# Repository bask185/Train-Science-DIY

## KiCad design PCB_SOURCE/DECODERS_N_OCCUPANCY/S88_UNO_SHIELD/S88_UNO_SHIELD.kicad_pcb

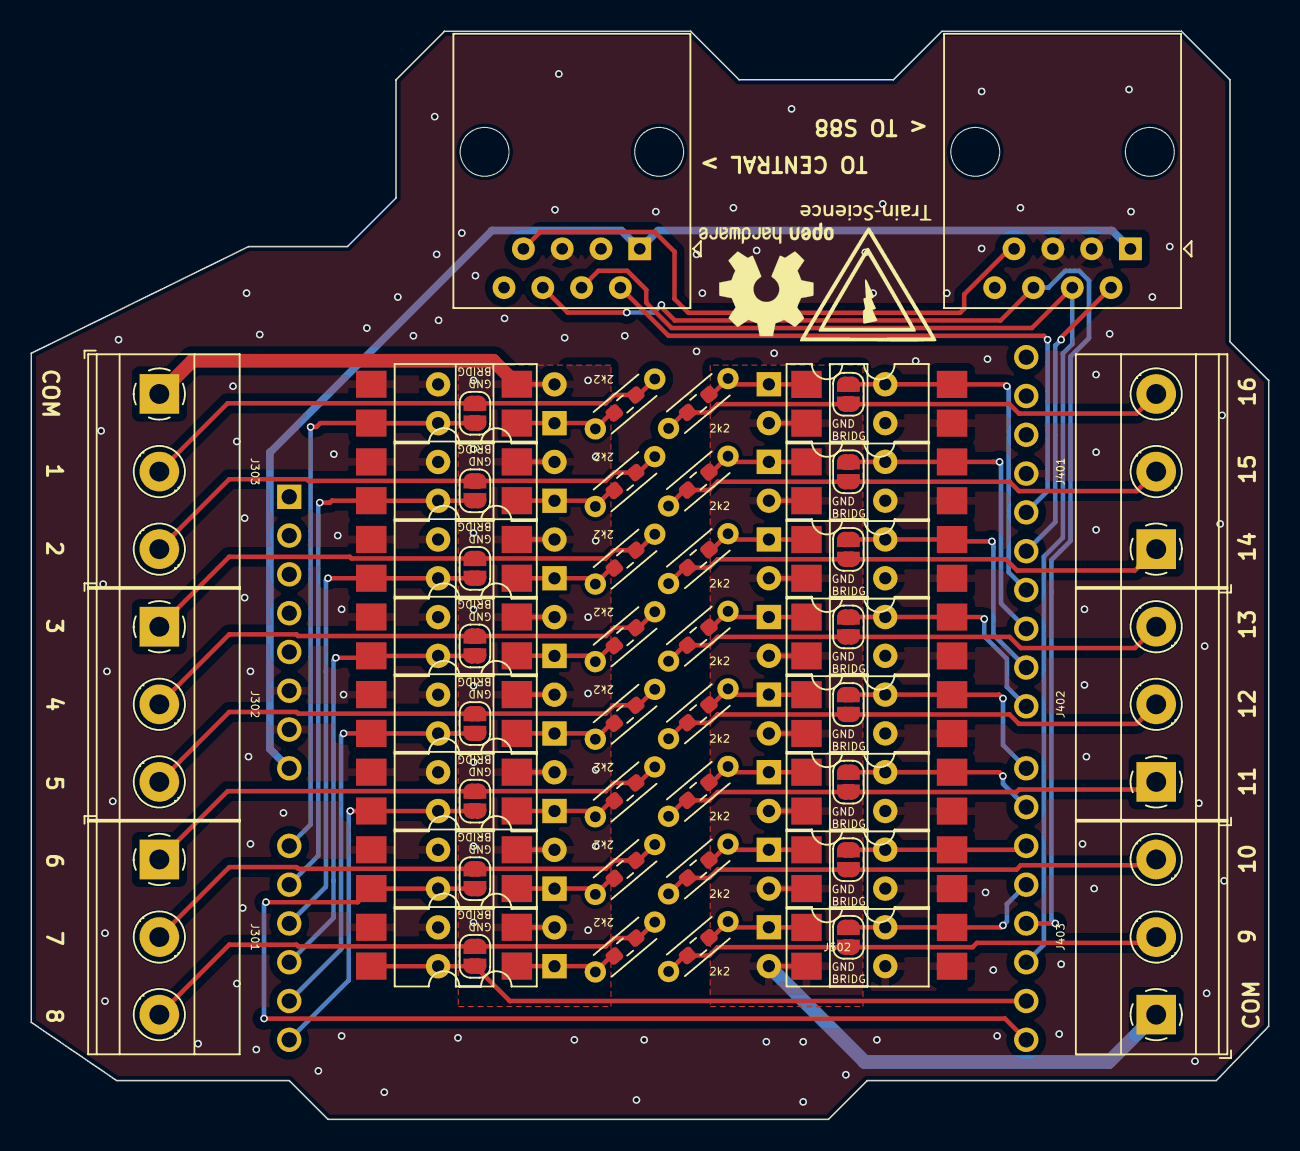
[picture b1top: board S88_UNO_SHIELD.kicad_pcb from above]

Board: 2 copper layers, 81.0 x 71.2 mm, 89 parts (1 on the bottom side), 57 nets.

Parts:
A201: Arduino_UNO_R3
J301, J302, J303, J401, J402, J403: Screw_Terminal_01x03; TerminalBlock_Phoenix_MKDS-1,5-3-5.08_1x03_P5.08mm_Horizont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
J501: RJ45_IN; RJ45_Amphenol_54602-x08_Horizontal
J502: RJ45_OUT; RJ45_Amphenol_54602-x08_Horizontal
JP601, JP701, JP801, JP901, JP1001, JP1101, JP1201, JP1301, JP1401, JP1501, JP1601, JP1701, JP1801, JP1901, JP2001, JP2101: GND VERSION; SolderJumper-2_P1.3mm_Open_RoundedPad1.0x1.5mm
R601, R701, R801, R901, R1001, R1101, R1201, R1301, R1401, R1501, R1601, R1701, R1801, R1901, R2001, R2101: 2k2; R_Axial_DIN0204_L3.6mm_D1.6mm_P5.08mm_Horizontal
R602, R702, R802, R902, R1002, R1102, R1202, R1302, R1402, R1502, R1602, R1702, R1802, R1902, R2002, R2102: 2k2; R_0603_smalltext
U601, U701, U801, U901, U1001, U1101, U1201, U1301, U1401, U1501, U1601, U1701, U1801, U1901, U2001, U2101: EL814S; SMDIP-4_W9.53mm
U602, U702, U802, U902, U1002, U1102, U1202, U1302, U1402, U1502, U1602, U1702, U1802, U1902, U2002, U2102: EL814; DIP-4_W7.62mm

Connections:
+12V: A201.8 (VIN), J501.1, J502.1
/GPIO_A/CS1/COM: J303.1, U601.2, U602.2, U701.2, U702.2, U801.2, U802.2, U901.2, U902.2, U1001.2, U1002.2, U1101.2, U1102.2, U1201.2, U1202.2, U1301.2, U1302.2
/GPIO_A/CS1/Track: J301.3, JP601.1 (A), R601.1, R602.1
/GPIO_A/CS2/Track: J301.2, JP701.1 (A), R701.1, R702.1
/GPIO_A/CS3/Track: J301.1, JP801.1 (A), R801.1, R802.1
/GPIO_A/CS4/Track: J302.3, JP901.1 (A), R901.1, R902.1
/GPIO_A/CS5/Track: J302.2, JP1001.1 (A), R1001.1, R1002.1
/GPIO_A/CS6/Track: J302.1, JP1101.1 (A), R1101.1, R1102.1
/GPIO_A/CS7/Track: J303.3, JP1201.1 (A), R1201.1, R1202.1
/GPIO_A/CS8/Track: J303.2, JP1301.1 (A), R1301.1, R1302.1
/GPIO_A/GPIO1: A201.9 (A0), JP1301.2 (B), U1301.4, U1302.4
/GPIO_A/GPIO2: A201.10 (A1), JP1201.2 (B), U1201.4, U1202.4
/GPIO_A/GPIO3: A201.11 (A2), JP1101.2 (B), U1101.4, U1102.4
/GPIO_A/GPIO4: A201.12 (A3), JP1001.2 (B), U1001.4, U1002.4
/GPIO_A/GPIO5: A201.13 (SDA/A4), JP901.2 (B), U901.4, U902.4
/GPIO_A/GPIO6: A201.14 (SCL/A5), JP801.2 (B), U801.4, U802.4
/GPIO_A/GPIO7: A201.15 (D0/RX), JP701.2 (B), U701.4, U702.4
/GPIO_A/GPIO8: A201.16 (D1/TX), JP601.2 (B), U601.4, U602.4
/GPIO_B/CS1/COM: J403.1, U1401.2, U1402.2, U1501.2, U1502.2, U1601.2, U1602.2, U1701.2, U1702.2, U1801.2, U1802.2, U1901.2, U1902.2, U2001.2, U2002.2, U2101.2, U2102.2
/GPIO_B/CS1/Track: J401.3, JP1401.1 (A), R1401.1, R1402.1
/GPIO_B/CS2/Track: J401.2, JP1501.1 (A), R1501.1, R1502.1
/GPIO_B/CS3/Track: J401.1, JP1601.1 (A), R1601.1, R1602.1
/GPIO_B/CS4/Track: J402.3, JP1701.1 (A), R1701.1, R1702.1
/GPIO_B/CS5/Track: J402.2, JP1801.1 (A), R1801.1, R1802.1
/GPIO_B/CS6/Track: J402.1, JP1901.1 (A), R1901.1, R1902.1
/GPIO_B/CS7/Track: J403.3, JP2001.1 (A), R2001.1, R2002.1
/GPIO_B/CS8/Track: J403.2, JP2101.1 (A), R2101.1, R2102.1
/GPIO_B/GPIO1: A201.19 (D4), JP2101.2 (B), U2101.4, U2102.4
/GPIO_B/GPIO2: A201.20 (D5), JP2001.2 (B), U2001.4, U2002.4
/GPIO_B/GPIO3: A201.21 (D6), JP1901.2 (B), U1901.4, U1902.4
/GPIO_B/GPIO4: A201.22 (D7), JP1801.2 (B), U1801.4, U1802.4
/GPIO_B/GPIO5: A201.23 (D8), JP1701.2 (B), U1701.4, U1702.4
/GPIO_B/GPIO6: A201.24 (D9), JP1601.2 (B), U1601.4, U1602.4
/GPIO_B/GPIO7: A201.25 (D10), JP1501.2 (B), U1501.4, U1502.4
/GPIO_B/GPIO8: A201.26 (D11), JP1401.2 (B), U1401.4, U1402.4
/S88n/CLOCK: A201.17 (D2), J501.4, J502.4
/S88n/DATA_IN: A201.27 (D12), J501.2
/S88n/DATA_OUT: A201.28 (D13), J502.2
/S88n/PL: A201.18 (D3), J501.6, J502.6
/S88n/RESET: J501.7, J502.7
GND: A201.6 (GND), A201.7 (GND), A201.29 (GND), J501.3, J501.5, J502.3, J502.5, U601.3, U602.3, U701.3, U702.3, U801.3, U802.3, U901.3, U902.3, U1001.3, U1002.3, U1101.3, U1102.3, U1201.3, U1202.3, U1301.3, U1302.3, U1401.3, U1402.3, U1501.3, U1502.3, U1601.3, U1602.3, U1701.3, U1702.3, U1801.3, U1802.3, U1901.3, U1902.3, U2001.3, U2002.3, U2101.3, U2102.3
unnamed: R601.2, R602.2, U601.1, U602.1
unnamed: R701.2, R702.2, U701.1, U702.1
unnamed: R801.2, R802.2, U801.1, U802.1
unnamed: R901.2, R902.2, U901.1, U902.1
unnamed: R1001.2, R1002.2, U1001.1, U1002.1
unnamed: R1101.2, R1102.2, U1101.1, U1102.1
unnamed: R1201.2, R1202.2, U1201.1, U1202.1
unnamed: R1301.2, R1302.2, U1301.1, U1302.1
unnamed: R1401.2, R1402.2, U1401.1, U1402.1
unnamed: R1501.2, R1502.2, U1501.1, U1502.1
unnamed: R1601.2, R1602.2, U1601.1, U1602.1
unnamed: R1701.2, R1702.2, U1701.1, U1702.1
unnamed: R1801.2, R1802.2, U1801.1, U1802.1
unnamed: R1901.2, R1902.2, U1901.1, U1902.1
unnamed: R2001.2, R2002.2, U2001.1, U2002.1
unnamed: R2101.2, R2102.2, U2101.1, U2102.1

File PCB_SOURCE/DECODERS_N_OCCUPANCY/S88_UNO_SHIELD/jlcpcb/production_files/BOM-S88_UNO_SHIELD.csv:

Comment,Designator,Footprint,LCSC
RJ45_IN,"J501,J502",RJ45_Amphenol_54602-x08_Horizontal,C3000197
2k2,"R1002,R1102,R1202,R1302,R1402,R1502,R1602,R1702,R1802,R1902,R2002,R2102,R602,R702,R802,R902",R_0603_smalltext,C4190
EL814S,"U1001,U1101,U1201,U1301,U1401,U1501,U1601,U1701,U1801,U1901,U2001,U2101,U601,U701,U801,U901",SMDIP-4_W9.53mm,C500388
Screw_Terminal_01x03,"J301,J302,J303,J401,J402,J403","TerminalBlock_Phoenix_MKDS-1,5-3-5.08_1x03_P5.08mm_Horizontal",C557666
Arduino_UNO_R3,A201,Arduino_UNO_R3,

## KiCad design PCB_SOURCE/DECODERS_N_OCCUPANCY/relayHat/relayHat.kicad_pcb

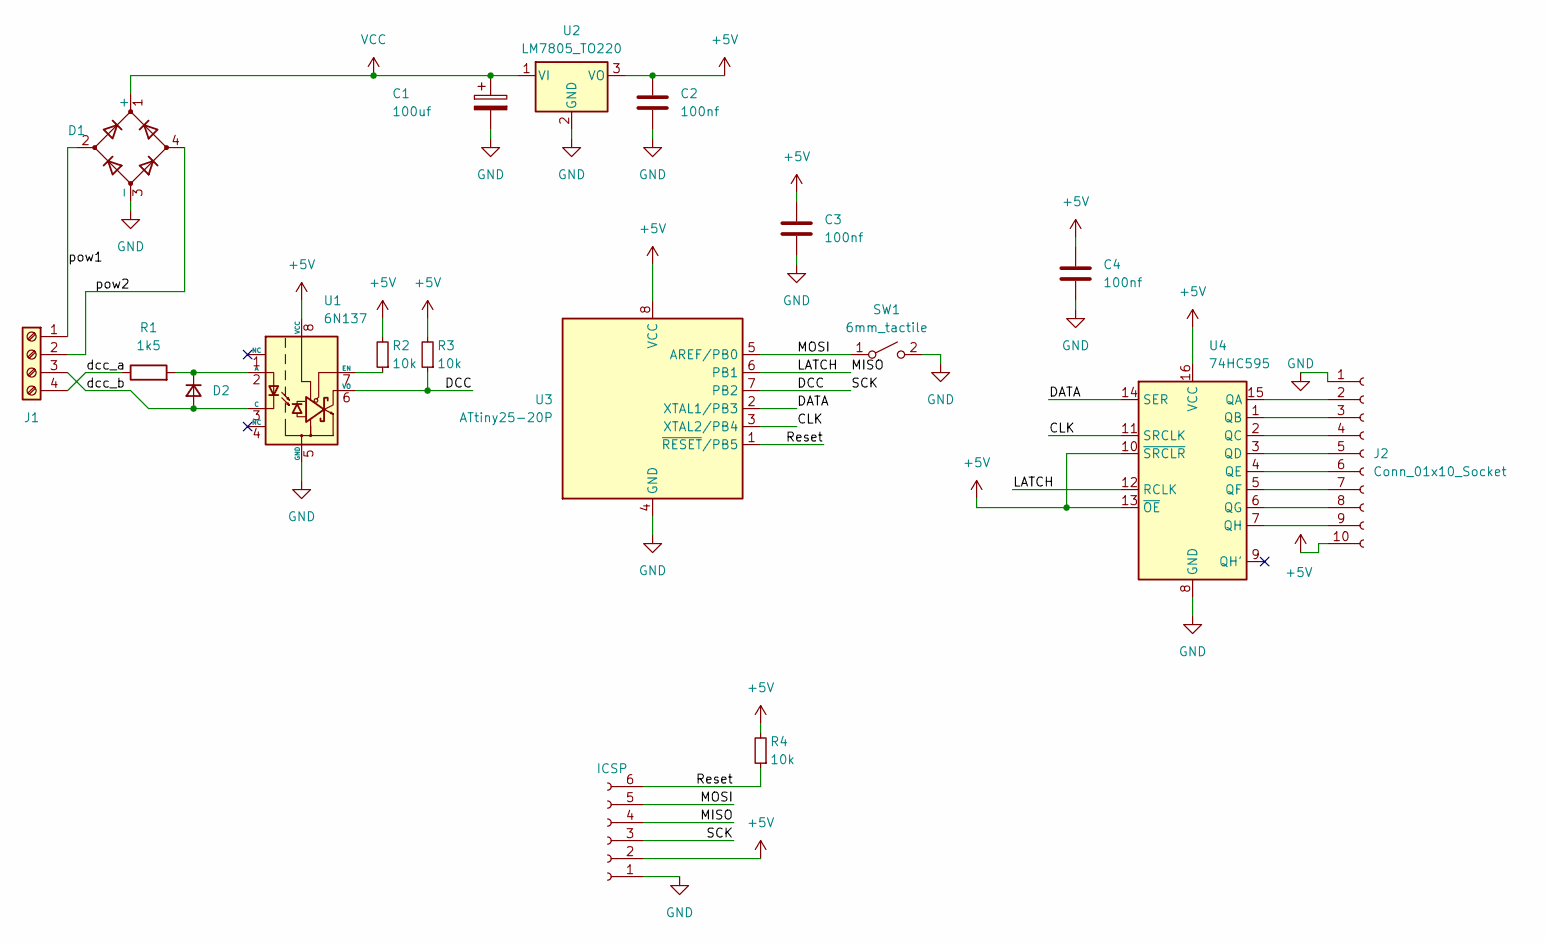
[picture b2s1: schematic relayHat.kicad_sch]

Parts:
C1: 100uf; CP_Radial_D5.0mm_P2.50mm
C2, C3, C4: 100nf; C_Disc_D3.0mm_W1.6mm_P2.50mm
D1: D_Bridge_+A-A; Diode_Bridge_Round_D8.9mm
D2: D_Small; D_DO-34_SOD68_P7.62mm_Horizontal
J1: Screw_Terminal_01x04; PhoenixContact_MC_1,5_4-G-3.5_1x04_P3.50mm_Horizontal
J2: Conn_01x10_Socket; PinSocket_1x10_P2.54mm_Vertical
J3: ICSP; PinHeader_1x06_P2.54mm_Vertical
R1: 1k5; R_Axial_DIN0204_L3.6mm_D1.6mm_P7.62mm_Horizontal
R2, R3, R4: 10k; R_Axial_DIN0204_L3.6mm_D1.6mm_P7.62mm_Horizontal
SW1: 6mm_tactile; SW_NO_SILK
U1: 6N137; DIP-8_W7.62mm
U2: LM7805_TO220; TO-220-3_Vertical
U3: ATtiny25-20P; DIP-8_W7.62mm
U4: 74HC595; DIP-16_W7.62mm

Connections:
+5V: C2.1, C3.1, C4.1, J2.10, J3.2, R2.2, R3.2, R4.2, U1.8 (VCC), U2.3 (VO), U3.8 (VCC), U4.10 (~SRCLR), U4.13 (~OE), U4.16 (VCC)
/CLK: U3.3 (XTAL2/PB4), U4.11 (SRCLK)
/DATA: U3.2 (XTAL1/PB3), U4.14 (SER)
/DCC: J3.3, R3.1, U1.6 (VO), U3.7 (PB2)
/LATCH: J3.4, U3.6 (PB1), U4.12 (RCLK)
/MOSI: J3.5, SW1.1 (A), U3.5 (AREF/PB0)
/Reset: J3.6, R4.1, U3.1 (~RESET/PB5)
/dcc_a: J1.4, R1.1
/dcc_b: D2.2 (A), J1.3, U1.3 (C)
/pow1: D1.2, J1.1
/pow2: D1.4, J1.2
GND: C1.2, C2.2, C3.2, C4.2, D1.3 (-), J2.1, J3.1, SW1.2 (B), U1.5 (GND), U2.2 (GND), U3.4 (GND), U4.8 (GND)
unnamed: D2.1 (K), R1.2, U1.2 (A)
unnamed: J2.2, U4.15 (QA)
unnamed: J2.3, U4.1 (QB)
unnamed: J2.4, U4.2 (QC)
unnamed: J2.5, U4.3 (QD)
unnamed: J2.6, U4.4 (QE)
unnamed: J2.7, U4.5 (QF)
unnamed: J2.8, U4.6 (QG)
unnamed: J2.9, U4.7 (QH)
unnamed: R2.1, U1.7 (EN)
VCC: C1.1, D1.1 (+), U2.1 (VI)

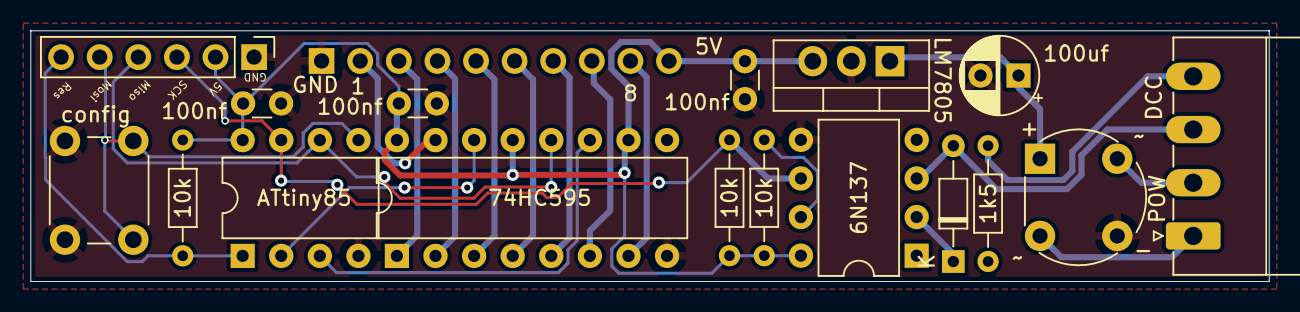
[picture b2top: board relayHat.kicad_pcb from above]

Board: 2 copper layers, 81.5 x 16.5 mm, 18 parts (1 on the bottom side), 23 nets.

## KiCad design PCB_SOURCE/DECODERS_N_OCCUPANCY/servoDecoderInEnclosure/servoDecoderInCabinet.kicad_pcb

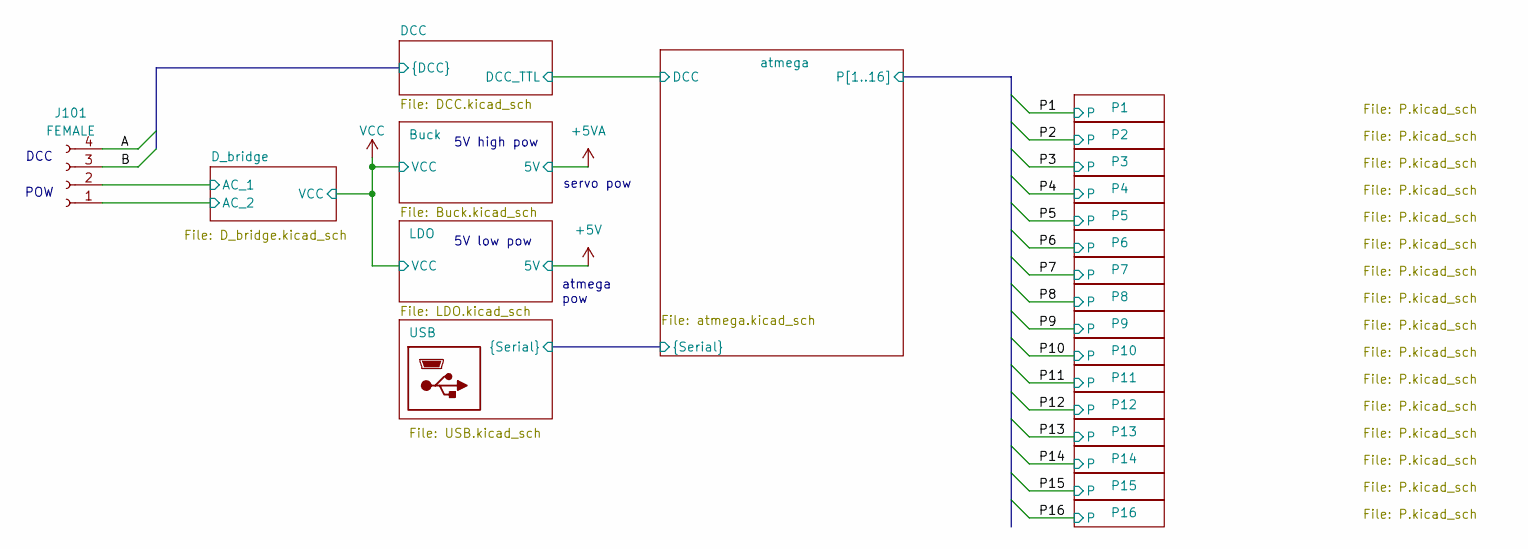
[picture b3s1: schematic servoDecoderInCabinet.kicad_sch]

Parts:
J101: FEMALE; PhoenixContact_MC_1,5_4-G-3.5_1x04_P3.50mm_Horizontal; JLCPCB Part# C880574
J102: USB_Mini_cosmetic

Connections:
/DCC/A: J101.4; also elsewhere on the board
/DCC/B: J101.3; also elsewhere on the board
/D_bridge/AC_1: J101.2; also elsewhere on the board
/D_bridge/AC_2: J101.1; also elsewhere on the board

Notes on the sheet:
5V high pow
5V low pow
DCC
atmega pow
servo pow
POW

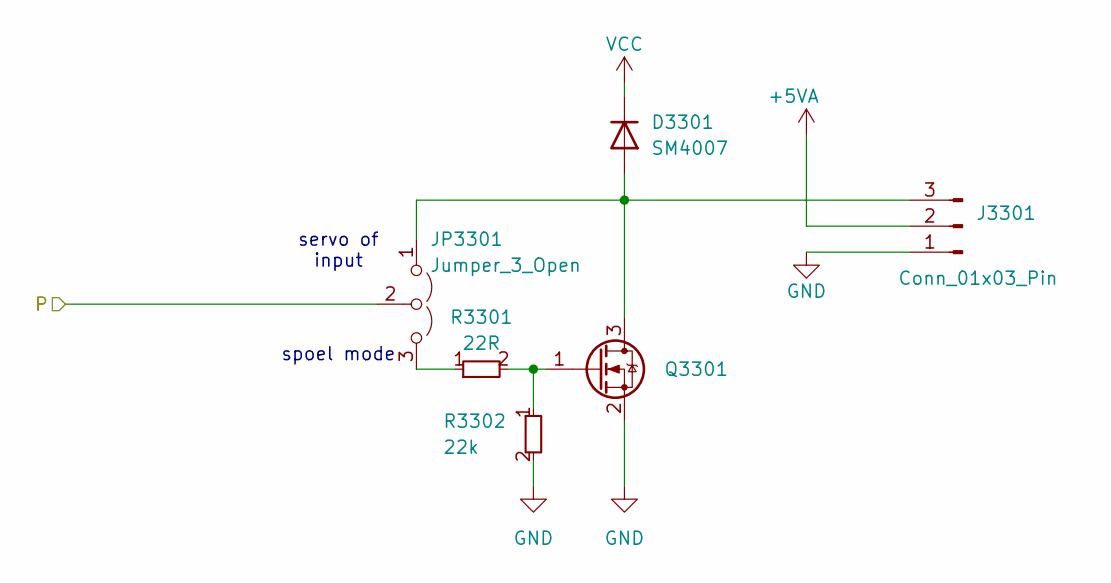
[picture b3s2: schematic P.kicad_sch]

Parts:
D3301: SM4007; D_SOD-123F; JLCPCB Part# C64898
J3301: Conn_01x03_Pin; PinHeader_1x03_P2.54mm_Vertical
JP3301: Jumper_3_Open; SolderJumper-3_P1.3mm_Open_RoundedPad1.0x1.5mm
Q3301: AO3400A; SOT-23; JLCPCB Part# C20917
R3301: 22R; R_0603_smalltext; JLCPCB Part# C23345
R3302: 22k; R_0603_smalltext; JLCPCB Part# C31850

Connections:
+5VA: J3301.2; also elsewhere on the board
/atmega/P13: JP3301.2 (C); also elsewhere on the board
GND: J3301.1, Q3301.2 (S), R3302.2; also elsewhere on the board
unnamed: D3301.2 (A), J3301.3, JP3301.1 (A), Q3301.3 (D)
unnamed: JP3301.3 (B), R3301.1
unnamed: Q3301.1 (G), R3301.2, R3302.1
VCC: D3301.1 (K); also elsewhere on the board

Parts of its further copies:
D2101, D2202, D2302, D2401, D2501, D2601, D2701, D2801, D2901, D3001, D3101, D3201, D3401, D3501, D3601: SM4007; D_SOD-123F; JLCPCB Part# C64898
J2101, J2202, J2302, J2401, J2501, J2601, J2701, J2801, J2901, J3001, J3101, J3201, J3401, J3501, J3601: Conn_01x03_Pin; PinHeader_1x03_P2.54mm_Vertical
JP2101, JP2202, JP2302, JP2401, JP2501, JP2601, JP2701, JP2801, JP2901, JP3001, JP3101, JP3201, JP3401, JP3501, JP3601: Jumper_3_Open; SolderJumper-3_P1.3mm_Open_RoundedPad1.0x1.5mm
Q2101, Q2202, Q2302, Q2401, Q2501, Q2601, Q2701, Q2801, Q2901, Q3001, Q3101, Q3201, Q3401, Q3501, Q3601: AO3400A; SOT-23; JLCPCB Part# C20917
R2101, R2203, R2303, R2401, R2501, R2601, R2701, R2801, R2901, R3001, R3101, R3201, R3401, R3501, R3601: 22R; R_0603_smalltext; JLCPCB Part# C23345
R2102, R2204, R2304, R2402, R2502, R2602, R2702, R2802, R2902, R3002, R3102, R3202, R3402, R3502, R3602: 22k; R_0603_smalltext; JLCPCB Part# C31850

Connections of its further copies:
+5VA: J2101.2, J2202.2, J2302.2, J2401.2, J2501.2, J2601.2, J2701.2, J2801.2, J2901.2, J3001.2, J3101.2, J3201.2, J3401.2, J3501.2, J3601.2; also elsewhere on the board
/atmega/P1: JP2101.2 (C); also elsewhere on the board
/atmega/P2: JP2202.2 (C); also elsewhere on the board
/atmega/P3: JP2302.2 (C); also elsewhere on the board
/atmega/P4: JP2401.2 (C); also elsewhere on the board
/atmega/P5: JP2501.2 (C); also elsewhere on the board
/atmega/P6: JP2601.2 (C); also elsewhere on the board
/atmega/P7: JP2701.2 (C); also elsewhere on the board
/atmega/P8: JP2801.2 (C); also elsewhere on the board
/atmega/P9: JP2901.2 (C); also elsewhere on the board
/atmega/P10: JP3001.2 (C); also elsewhere on the board
/atmega/P11: JP3101.2 (C); also elsewhere on the board
/atmega/P12: JP3201.2 (C); also elsewhere on the board
/atmega/P14: JP3401.2 (C); also elsewhere on the board
/atmega/P15: JP3501.2 (C); also elsewhere on the board
/atmega/P16: JP3601.2 (C); also elsewhere on the board
GND: J2101.1, J2202.1, J2302.1, J2401.1, J2501.1, J2601.1, J2701.1, J2801.1, J2901.1, J3001.1, J3101.1, J3201.1, J3401.1, J3501.1, J3601.1, Q2101.2 (S), Q2202.2 (S), Q2302.2 (S), Q2401.2 (S), Q2501.2 (S), Q2601.2 (S), Q2701.2 (S), Q2801.2 (S), Q2901.2 (S), Q3001.2 (S), Q3101.2 (S), Q3201.2 (S), Q3401.2 (S), Q3501.2 (S), Q3601.2 (S), R2102.2, R2204.2, R2304.2, R2402.2, R2502.2, R2602.2, R2702.2, R2802.2, R2902.2, R3002.2, R3102.2, R3202.2, R3402.2, R3502.2, R3602.2; also elsewhere on the board
unnamed: D2101.2 (A), J2101.3, JP2101.1 (A), Q2101.3 (D)
unnamed: D2202.2 (A), J2202.3, JP2202.1 (A), Q2202.3 (D)
unnamed: D2302.2 (A), J2302.3, JP2302.1 (A), Q2302.3 (D)
unnamed: D2401.2 (A), J2401.3, JP2401.1 (A), Q2401.3 (D)
unnamed: D2501.2 (A), J2501.3, JP2501.1 (A), Q2501.3 (D)
unnamed: D2601.2 (A), J2601.3, JP2601.1 (A), Q2601.3 (D)
unnamed: D2701.2 (A), J2701.3, JP2701.1 (A), Q2701.3 (D)
unnamed: D2801.2 (A), J2801.3, JP2801.1 (A), Q2801.3 (D)
unnamed: D2901.2 (A), J2901.3, JP2901.1 (A), Q2901.3 (D)
unnamed: D3001.2 (A), J3001.3, JP3001.1 (A), Q3001.3 (D)
unnamed: D3101.2 (A), J3101.3, JP3101.1 (A), Q3101.3 (D)
unnamed: D3201.2 (A), J3201.3, JP3201.1 (A), Q3201.3 (D)
unnamed: D3401.2 (A), J3401.3, JP3401.1 (A), Q3401.3 (D)
unnamed: D3501.2 (A), J3501.3, JP3501.1 (A), Q3501.3 (D)
unnamed: D3601.2 (A), J3601.3, JP3601.1 (A), Q3601.3 (D)
unnamed: JP2101.3 (B), R2101.1
unnamed: JP2202.3 (B), R2203.1
unnamed: JP2302.3 (B), R2303.1
unnamed: JP2401.3 (B), R2401.1
unnamed: JP2501.3 (B), R2501.1
unnamed: JP2601.3 (B), R2601.1
unnamed: JP2701.3 (B), R2701.1
unnamed: JP2801.3 (B), R2801.1
unnamed: JP2901.3 (B), R2901.1
unnamed: JP3001.3 (B), R3001.1
unnamed: JP3101.3 (B), R3101.1
unnamed: JP3201.3 (B), R3201.1
unnamed: JP3401.3 (B), R3401.1
unnamed: JP3501.3 (B), R3501.1
unnamed: JP3601.3 (B), R3601.1
unnamed: Q2101.1 (G), R2101.2, R2102.1
unnamed: Q2202.1 (G), R2203.2, R2204.1
unnamed: Q2302.1 (G), R2303.2, R2304.1
unnamed: Q2401.1 (G), R2401.2, R2402.1
unnamed: Q2501.1 (G), R2501.2, R2502.1
unnamed: Q2601.1 (G), R2601.2, R2602.1
unnamed: Q2701.1 (G), R2701.2, R2702.1
unnamed: Q2801.1 (G), R2801.2, R2802.1
unnamed: Q2901.1 (G), R2901.2, R2902.1
unnamed: Q3001.1 (G), R3001.2, R3002.1
unnamed: Q3101.1 (G), R3101.2, R3102.1
unnamed: Q3201.1 (G), R3201.2, R3202.1
unnamed: Q3401.1 (G), R3401.2, R3402.1
unnamed: Q3501.1 (G), R3501.2, R3502.1
unnamed: Q3601.1 (G), R3601.2, R3602.1
VCC: D2101.1 (K), D2202.1 (K), D2302.1 (K), D2401.1 (K), D2501.1 (K), D2601.1 (K), D2701.1 (K), D2801.1 (K), D2901.1 (K), D3001.1 (K), D3101.1 (K), D3201.1 (K), D3401.1 (K), D3501.1 (K), D3601.1 (K); also elsewhere on the board

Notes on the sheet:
servo of input
spoel mode

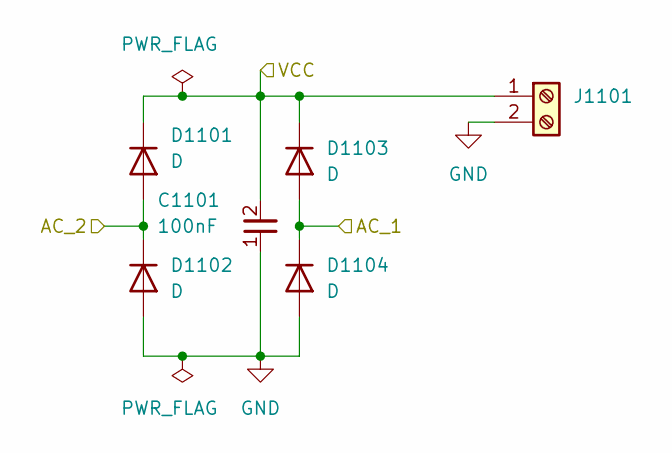
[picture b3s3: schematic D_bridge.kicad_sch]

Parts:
C1101: 100nF; C_0402_1005Metric; JLCPCB Part# C307331
D1101, D1102, D1103, D1104: D; D_SMA; JLCPCB Part# C22452
J1101: Screw_Terminal_01x02; PhoenixContact_MC_1,5_2-G-3.5_1x02_P3.50mm_Horizontal; JLCPCB Part# C880572

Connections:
/D_bridge/AC_1: D1103.2 (A), D1104.1 (K); also elsewhere on the board
/D_bridge/AC_2: D1101.2 (A), D1102.1 (K); also elsewhere on the board
GND: C1101.1, D1102.2 (A), D1104.2 (A), J1101.2; also elsewhere on the board
VCC: C1101.2, D1101.1 (K), D1103.1 (K), J1101.1; also elsewhere on the board

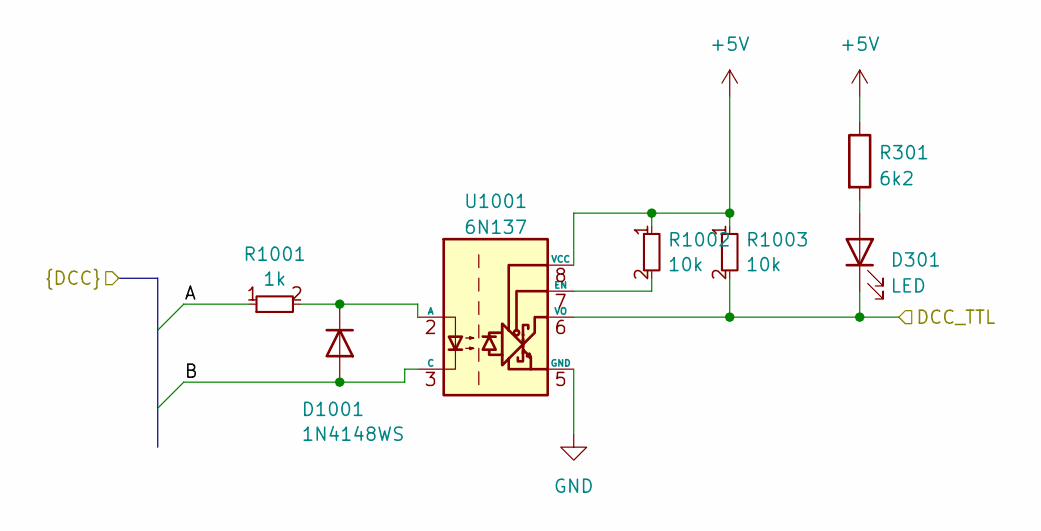
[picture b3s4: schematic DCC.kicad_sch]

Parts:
D301: LED; LED_0805_2012Metric_Pad1.15x1.40mm_HandSolder; JLCPCB Part# C84256
D1001: 1N4148WS; D_SOD-323; JLCPCB Part# C2128
R301: 6k2; R_0603_1608Metric_Pad0.98x0.95mm_HandSolder; JLCPCB Part# C4260
R1001: 1k; R_0603_smalltext; JLCPCB Part# C21190
R1002, R1003: 10k; R_0603_smalltext; JLCPCB Part# C25804
U1001: 6N137; SOP-8_6.62x9.15mm_P2.54mm; JLCPCB Part# C110020

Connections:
+5V: R301.1, R1002.1, R1003.1, U1001.8 (VCC); also elsewhere on the board
/DCC/A: R1001.1; also elsewhere on the board
/DCC/B: D1001.2 (A), U1001.3 (C); also elsewhere on the board
/DCC/DCC_TTL: D301.1 (K), R1003.2, U1001.6 (VO); also elsewhere on the board
GND: U1001.5 (GND); also elsewhere on the board
unnamed: D301.2 (A), R301.2
unnamed: D1001.1 (K), R1001.2, U1001.2 (A)
unnamed: R1002.2, U1001.7 (EN)

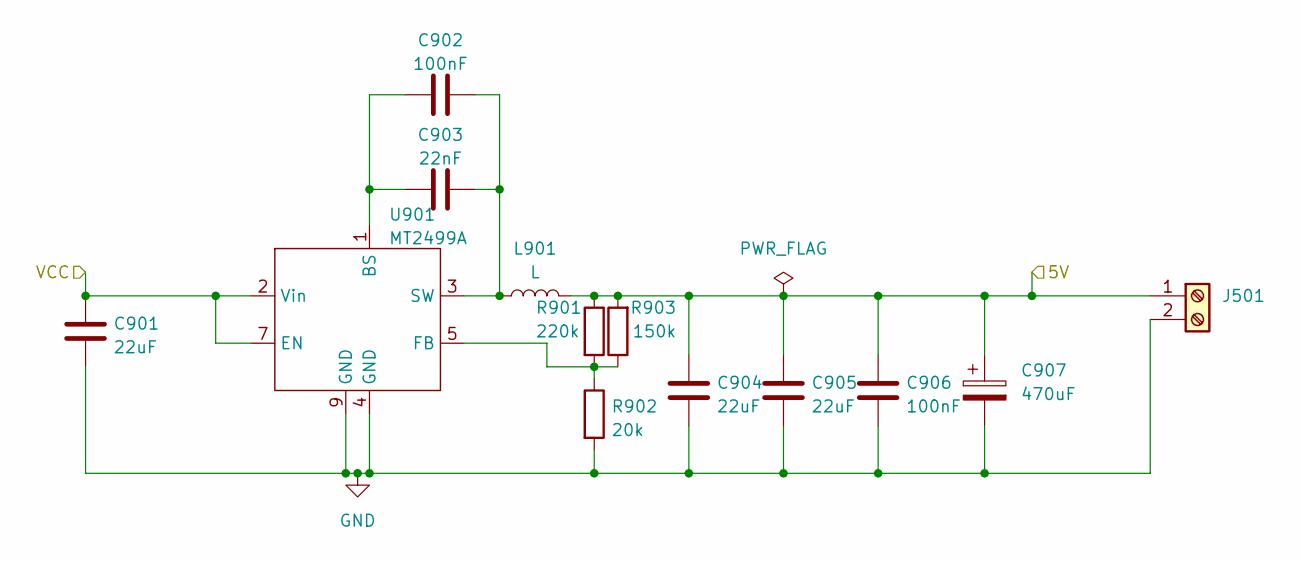
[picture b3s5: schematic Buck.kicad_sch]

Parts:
C901, C904, C905: 22uF; C_0603_1608Metric; JLCPCB Part# C45783
C902, C906: 100nF; C_0402_1005Metric; JLCPCB Part# C307331
C903: 22nF; C_0402_1005Metric; JLCPCB Part# C1532
C907: 470uF; CP_Elec_6.3x7.7; JLCPCB Part# C114446
J501: Screw_Terminal_01x02; PhoenixContact_MC_1,5_2-G-3.5_1x02_P3.50mm_Horizontal; JLCPCB Part# C880572
L901: L; L_Bourns-SRN8040_8x8.15mm; JLCPCB Part# C2929438
R901: 220k; R_0603_1608Metric; JLCPCB Part# C22961
R902: 20k; R_0603_1608Metric; JLCPCB Part# C4328
R903: 150k; R_0603_1608Metric; JLCPCB Part# C22807
U901: MT2499A; TI_SO-PowerPAD-8; JLCPCB Part# C3007555

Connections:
+5VA: C904.1, C905.1, C906.1, C907.1, J501.1, L901.2, R901.1, R903.2; also elsewhere on the board
GND: C901.2, C904.2, C905.2, C906.2, C907.2, J501.2, R902.2, U901.4 (GND), U901.9 (GND); also elsewhere on the board
unnamed: C902.1, C903.1, U901.1 (BS)
unnamed: R901.2, R902.1, R903.1, U901.5 (FB)
unnamed: C902.2, C903.2, L901.1, U901.3 (SW)
VCC: C901.1, U901.2 (Vin), U901.7 (EN); also elsewhere on the board

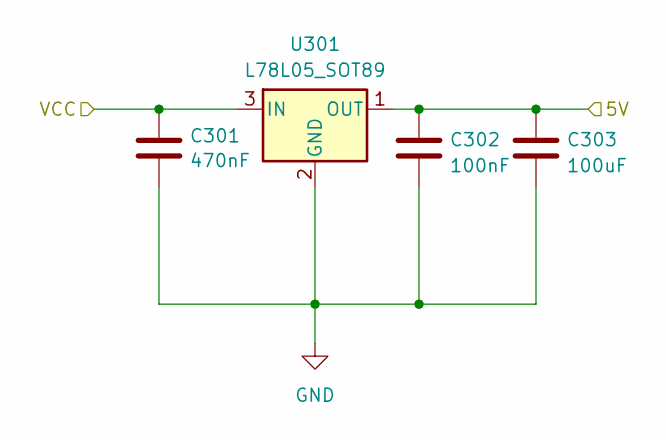
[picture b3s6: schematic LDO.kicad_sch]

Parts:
C301: 470nF; C_0805_2012Metric; JLCPCB Part# C13967
C302: 100nF; C_0603_1608Metric_Pad1.08x0.95mm_HandSolder; JLCPCB Part# C14663
C303: 100uF; C_1206_3216Metric_Pad1.33x1.80mm_HandSolder; JLCPCB Part# C15008
U301: L78L05_SOT89; SOT-89-3; JLCPCB Part# C71136

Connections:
+5V: C302.1, C303.1, U301.1 (OUT); also elsewhere on the board
GND: C301.2, C302.2, C303.2, U301.2 (GND); also elsewhere on the board
VCC: C301.1, U301.3 (IN); also elsewhere on the board

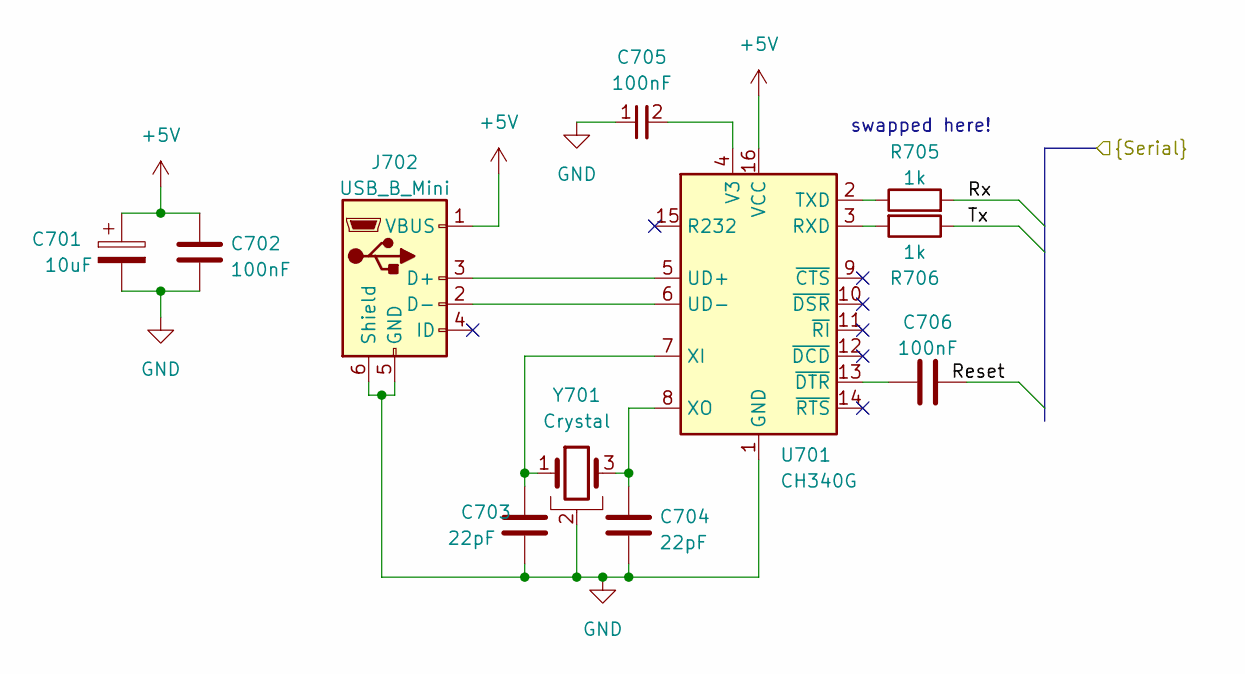
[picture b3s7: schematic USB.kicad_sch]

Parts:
C701: 10uF; C_0603_1608Metric; JLCPCB Part# C96446
C702, C706: 100nF; C_0603_1608Metric; JLCPCB Part# C14663
C703, C704: 22pF; C_0603_1608Metric; JLCPCB Part# C1653
C705: 100nF; C_0402_1005Metric; JLCPCB Part# C307331
J702: USB_B_Mini; USB_Mini-B_Lumberg_2486_01_Horizontal; JLCPCB Part# C2681563
R705, R706: 1k; R_0603_1608Metric; JLCPCB Part# C21190
U701: CH340G; SOIC-16_3.9x9.9mm_P1.27mm; JLCPCB Part# C14267
Y701: Crystal; crystal_arduino; JLCPCB Part# C9002

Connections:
+5V: C701.1, C702.1, J702.1 (VBUS), U701.16 (VCC); also elsewhere on the board
/USB/Reset: C706.2; also elsewhere on the board
/USB/Rx: R705.2; also elsewhere on the board
/USB/Tx: R706.1; also elsewhere on the board
GND: C701.2, C702.2, C703.2, C704.2, C705.1, J702.5 (GND), J702.6 (Shield), U701.1 (GND), Y701.2 (GND), Y701.4 (GND); also elsewhere on the board
unnamed: J702.3 (D+), U701.5 (UD+)
unnamed: J702.2 (D-), U701.6 (UD-)
unnamed: R706.2, U701.3 (RXD)
unnamed: R705.1, U701.2 (TXD)
unnamed: C705.2, U701.4 (V3)
unnamed: C703.1, U701.7 (XI), Y701.1
unnamed: C704.1, U701.8 (XO), Y701.3
unnamed: C706.1, U701.13 (~DTR)

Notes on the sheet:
swapped here!

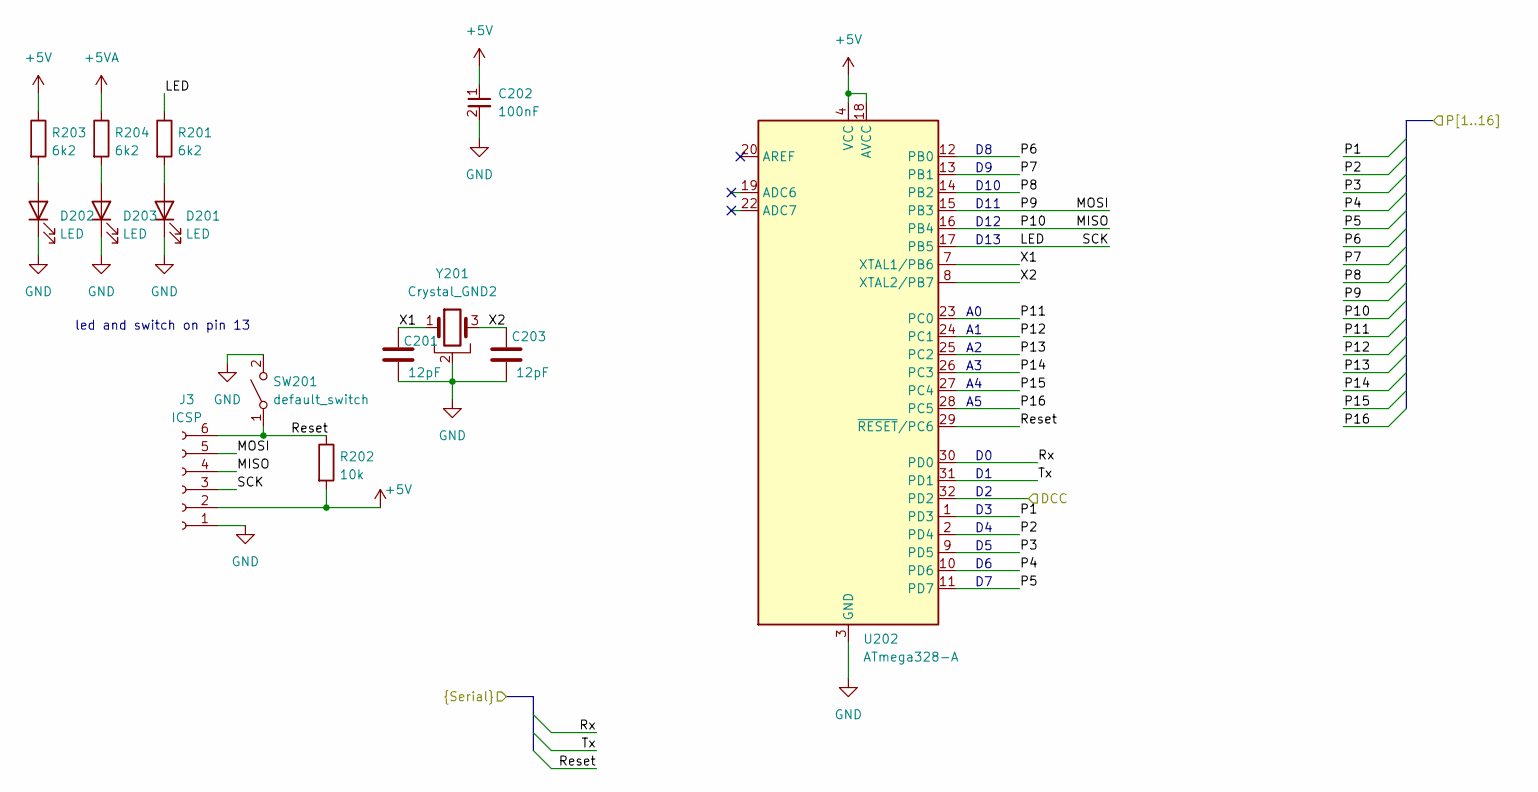
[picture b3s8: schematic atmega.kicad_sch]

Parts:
C201, C203: 12pF; C_0603_1608Metric; JLCPCB Part# C38523
C202: 100nF; C_0402_1005Metric; JLCPCB Part# C307331
D201, D202, D203: LED; LED_0805_2012Metric_Pad1.15x1.40mm_HandSolder; JLCPCB Part# C84256
J3: ICSP; PinHeader_1x06_P2.54mm_Vertical
R201, R203, R204: 6k2; R_0603_1608Metric_Pad0.98x0.95mm_HandSolder; JLCPCB Part# C4260
R202: 10k; R_0402_1005Metric_Pad0.72x0.64mm_HandSolder; JLCPCB Part# C25744
SW201: default_switch; JLCPCB Part# C318884
U202: ATmega328-A; TQFP-32_7x7mm_P0.8mm; JLCPCB Part# C14877
Y201: Crystal_GND2; crystal_arduino; JLCPCB Part# C13738

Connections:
+5V: C202.1, R202.2, R203.1, U202.4 (VCC), U202.6 (VCC), U202.18 (AVCC); also elsewhere on the board
+5VA: R204.1; also elsewhere on the board
/DCC/DCC_TTL: U202.32 (PD2); also elsewhere on the board
/USB/Reset: R202.1, SW201.1 (A), U202.29 (~RESET/PC6); also elsewhere on the board
/USB/Rx: U202.30 (PD0); also elsewhere on the board
/USB/Tx: U202.31 (PD1); also elsewhere on the board
/atmega/LED: R201.1, U202.17 (PB5); also elsewhere on the board
/atmega/P1: U202.1 (PD3); also elsewhere on the board
/atmega/P2: U202.2 (PD4); also elsewhere on the board
/atmega/P3: U202.9 (PD5); also elsewhere on the board
/atmega/P4: U202.10 (PD6); also elsewhere on the board
/atmega/P5: U202.11 (PD7); also elsewhere on the board
/atmega/P6: U202.12 (PB0); also elsewhere on the board
/atmega/P7: U202.13 (PB1); also elsewhere on the board
/atmega/P8: U202.14 (PB2); also elsewhere on the board
/atmega/P9: U202.15 (PB3); also elsewhere on the board
/atmega/P10: U202.16 (PB4); also elsewhere on the board
/atmega/P11: U202.23 (PC0); also elsewhere on the board
/atmega/P12: U202.24 (PC1); also elsewhere on the board
/atmega/P13: U202.25 (PC2); also elsewhere on the board
/atmega/P14: U202.26 (PC3); also elsewhere on the board
/atmega/P15: U202.27 (PC4); also elsewhere on the board
/atmega/P16: U202.28 (PC5); also elsewhere on the board
/atmega/X1: C201.2, U202.7 (XTAL1/PB6), Y201.1
/atmega/X2: C203.2, U202.8 (XTAL2/PB7), Y201.3
GND: C201.1, C202.2, C203.1, D201.1 (K), D202.1 (K), D203.1 (K), SW201.2 (B), U202.3 (GND), U202.5 (GND), U202.21 (GND), Y201.2 (GND), Y201.4 (GND); also elsewhere on the board
unnamed: D201.2 (A), R201.2
unnamed: D202.2 (A), R203.2
unnamed: D203.2 (A), R204.2

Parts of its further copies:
J201: ICSP; PinHeader_1x06_P2.54mm_Vertical

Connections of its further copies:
+5V: J201.2; also elsewhere on the board
/USB/Reset: J201.6; also elsewhere on the board
/atmega/LED: J201.3; also elsewhere on the board
/atmega/P9: J201.5; also elsewhere on the board
/atmega/P10: J201.4; also elsewhere on the board
GND: J201.1; also elsewhere on the board

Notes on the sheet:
D13
D12
D10
D11
led and switch on pin 13
